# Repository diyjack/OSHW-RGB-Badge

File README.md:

# OSHW-RGB-Badge
Badge with RGB-LED and [OSHW (Open Source Hardware)](http://www.oshwa.org/open-source-hardware-logo/) Design.

**Assembly Instructions:**
[German](https://raw.github.com/watterott/OSHW-RGB-Badge/master/pcb/OSHW-RGB-Badge_de.pdf)

## Shop
* [OSHW-RGB-Badge](http://www.watterott.com/en/OSHW-RGB-Badge)

## Videos
*

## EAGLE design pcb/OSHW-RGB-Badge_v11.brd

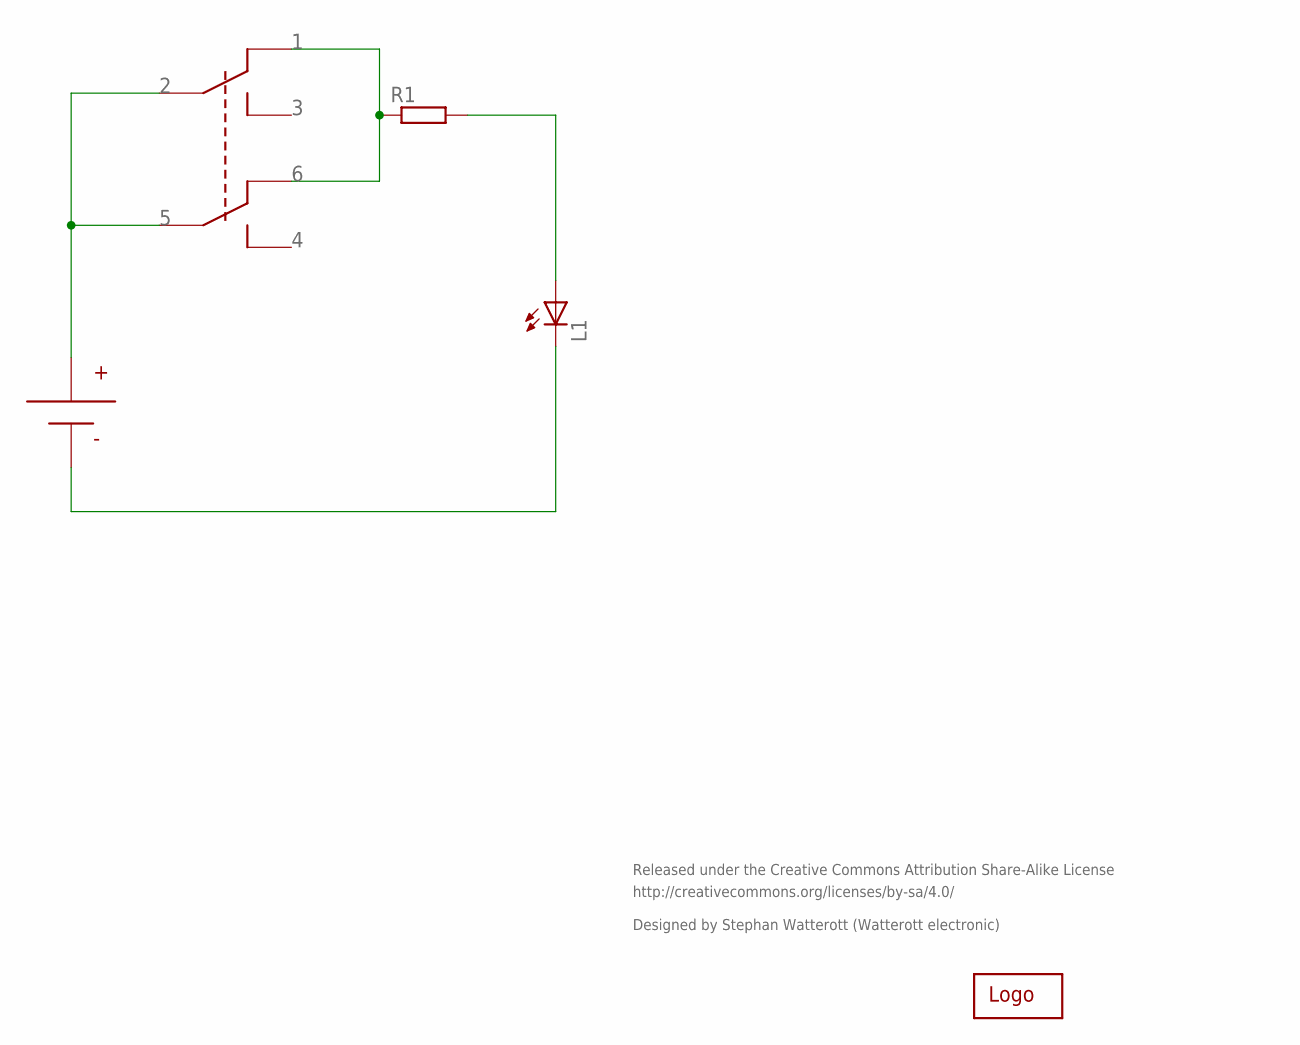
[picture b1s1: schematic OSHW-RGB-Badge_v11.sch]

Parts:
BAT: CN2032_BATTERY_HOLDER
L1: LED10MM
LOGO3: LOGO-SPARK_PLACE; SPARK_TPLACE
R1: R-EU_0207/7; 0207/7
SW: SWITCH_6-POL_RM2.54; SWITCH_6POL_RM2.54

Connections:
unnamed: R1.1, SW.P$1, SW.P$6
unnamed: BAT.P$1 (+), SW.P$2, SW.P$5
unnamed: L1.A, R1.2
unnamed: BAT.P$2 (-), L1.K (C)

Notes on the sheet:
Released under the Creative Commons Attribution Share-Alike License
http://creativecommons.org/licenses/by-sa/4.0/
Designed by Stephan Watterott (Watterott electronic)

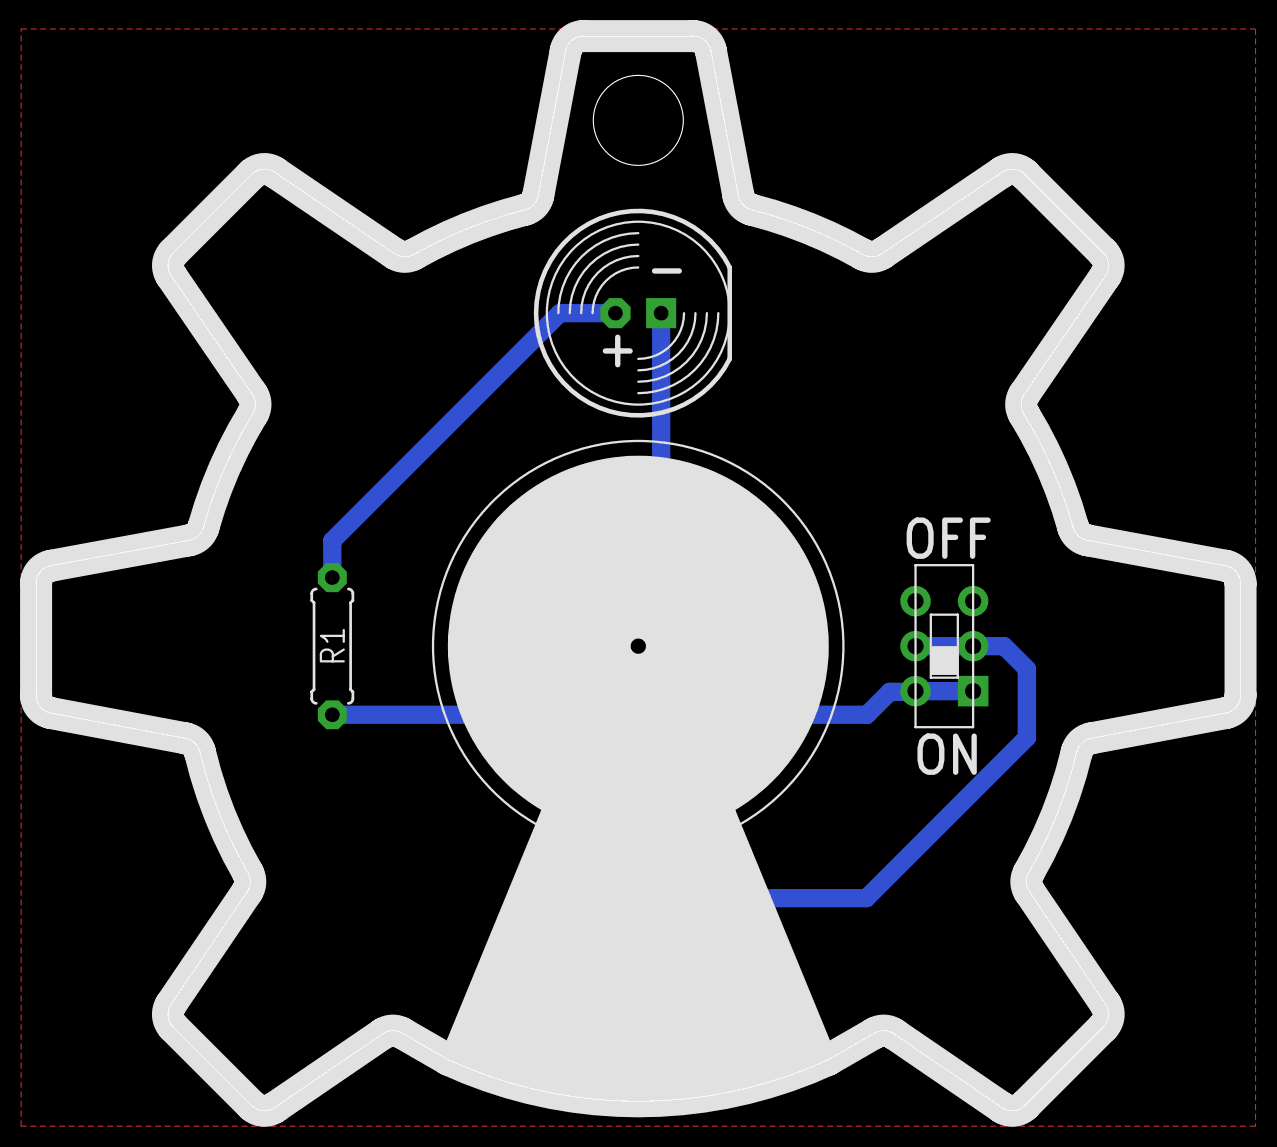
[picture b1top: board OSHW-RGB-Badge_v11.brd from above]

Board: 2 copper layers, 66.9 x 59.7 mm, 5 parts (1 on the bottom side), 4 nets.

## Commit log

2014-03-20 added schematics and layout files
2014-06-11 added OSHW logo
2014-07-07 optimized board layout
2014-07-30 added assembly instructions
2014-08-05 added new schematics and layout files
2014-08-21 updated layout and schematics
2014-09-25 updated image
2014-11-06 cleaned up schematics and layout
2015-01-11 moved image
